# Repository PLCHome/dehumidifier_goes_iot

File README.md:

# My dehumidifier becomes an IoT device

**Please note that opening electrical devices is life-threatening! Opening electrical devices and working on them requires training and authorization.**

**Never work on devices connected to the electrical grid, regardless of whether they are turned on or off.**

**If you follow or replicate parts of this description, you do so entirely at your own risk. I am not liable for any damage caused, including damage to your health and life.**

### Introduction

I've had this TROTEC TTK70 device for many years. It helps me keep my basement dry in the summer.
You can, of course, turn the dehumidifier on every day and let it run for a few hours.
My problem is that I want to use the power from the PV system for this. However, since I leave the house at 6:30 a.m., it doesn't generate enough electricity, depending on the time of year.
At first, I considered using a timer. But this device only beeps once and then stops working when the power comes back on.

## Implementation

**Working with electricity is your own responsibility. I am not liable for any damage, including damage to your health.**

Since the circuit diagram attached to the side was also not informative

I took a look at the device from the inside and noticed that there was a control panel. I drew its circuit diagram and considered how it might work.

The connector has 8 contacts. You can see from the diodes that 1, 2, and 4 are positive, and 3, 5, 6, and 7 are negative.

Since not all LEDs light up at the same time, there must be a control system behind them. I figured that the microcontroller in the device connects lines 3, 5, 6, and 7 to negative one after the other and turns on lines 1, 2, and 4 at the right moment to turn on the LED. We'll refer to lines 3, 5, 6, and 7 as rotating lines.

That leaves the three buttons and line 8. The diodes are there to prevent the wrong LEDs from lighting up when two buttons are pressed at once. And the function is also somewhat instructive. If you pull line eight high with a pull-up resistor, it goes low when the connected rotating line goes negative and the button is pressed.

The only remaining issue is the power supply. However, since the dehumidifier has a transformer built in that always supplies 12V AC when plugged in, that was quickly resolved. Just connect two wires to the output of the rectifier circuit; that's it.

So I gathered a few parts from my stash and started experimenting on the bash board.

I quickly decided to try it with ESPHome and an ESP32-S3 mini that was lying on my desk.

The main problem with the dehumidifier is a microcontroller connected to an LS7805. The ESP32 only requires 3.3V on the GPIOs. If I connect the ESP32 to the same ground via the voltage converter and place the data lines on 3.3V pull-up resistors like the manufacturer did with the buttons, it should work. I didn't even need to solder the pull-ups. They're already built into the ESP32. While lengthening the pins, I noticed that I have two ESP32s that are identical in size but not identical. I have an ESP32-S3 mini and an ESP32-S3 tiny. It's important to note that GPIO 3 is in a different location on both. Since there are boot issues with this GPIO, you shouldn't use GPIO 3. Furthermore, the ESP32-S3 tiny must be installed upside down. Since an ESP32 connected to a 3.3V supply died in another project, I'm now only using 5V voltage converters. However, it seems to be recommended that the ESP generate the 3.3V itself.

Simple transistors should be sufficient for the buttons. Since I don't know the breakdown voltages, I preferred to use diodes there.

Oh, the diodes don't really matter, just like the transistors. I had a large pile of them in stock here. But any other NPN transistor or any other diode will work.

I didn't feel like drawing the ESP, and I couldn't find a finished one. So I just used two connectors.

A friend was kind enough to mill a circuit board for me on his CNC milling machine. It looks a bit better than a perforated board.

After inserting the board into the device, the ESP32 rebooted every time I turned the device on and off. This wasn't good. I then used the other controller from Waveshare. This one also requires upside-down installation and has a different GPIO order. I adjusted the layout so that it now works with both. I modified the underside of the board. The dead copper surface was quite useful here. It works with this one. I also added the capacitor to the board because I was trying to use it to prevent the mini ESP32 from booting. But it seems to be the proximity to the relays and not the supply voltage. The capacitor is 2200uF and is connected to the 5V line to the controller.

## ESPHome and the homeassist

And then the YAML for ESP Home, and here it is in Home Assistant. You can select one of the four modes and OFF using the top selection. The one below allows you to select the integrated timers 2H, 4H, 8H, and OFF. After the controller has selected the setting, it resets to "–" which means nothing is selected there. The states are displayed below as text sensors. There are also two binary sensors for on and water tank full.

When you select a mode, the ESP first checks whether the device is on or off and presses the power button if necessary. The ESP32 then presses the mode button repeatedly until the correct mode is selected.

For the timer, it presses the timer button repeatedly until the selection is made.

Press a button? Not really, it controls the transistors, but to the microcontroller in the dehumidifier, it looks like a button press...

**Working with electricity is your own responsibility. I am not liable for any damage, including damage to your health.**

Do you have such great projects? Write me...

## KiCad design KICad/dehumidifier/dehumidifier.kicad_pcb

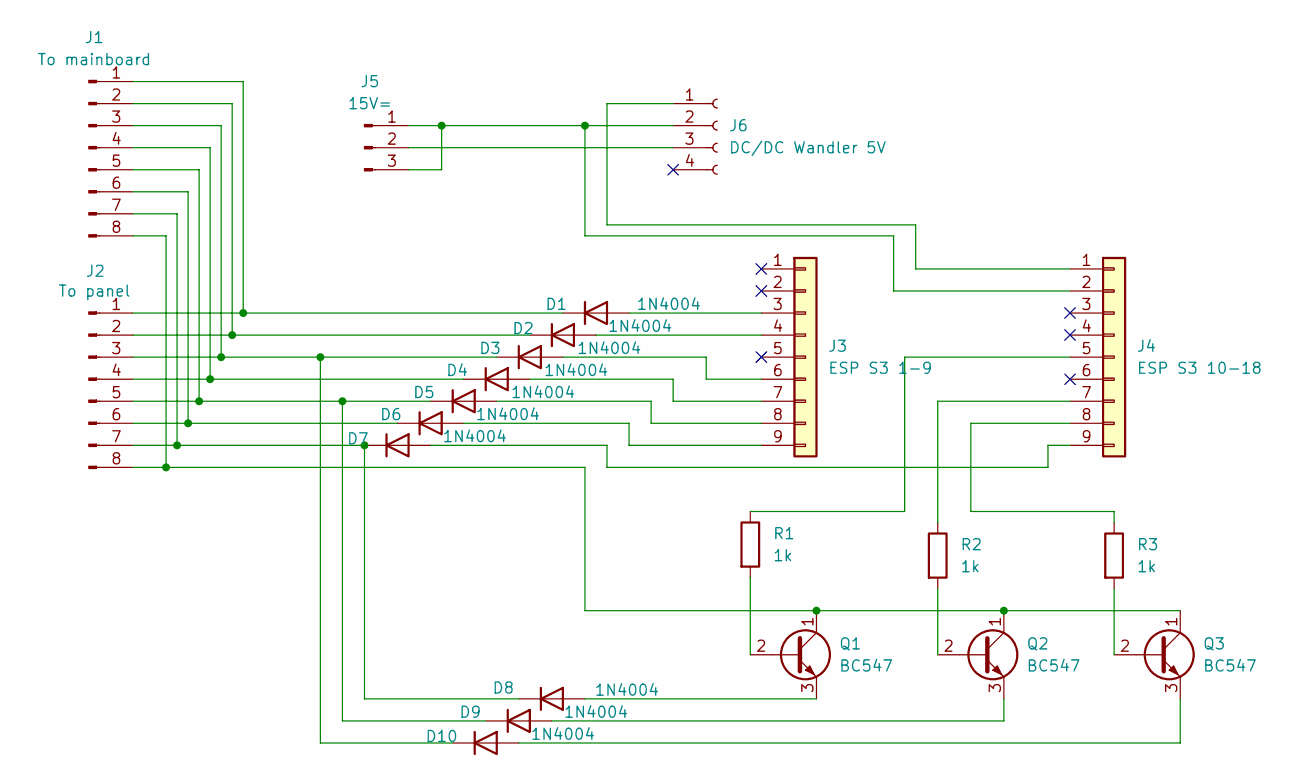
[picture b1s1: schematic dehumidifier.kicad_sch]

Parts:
D1, D2, D3, D4, D5, D6, D7, D8, D9, D10: 1N4004; D_DO-34_SOD68_P7.62mm_Horizontal
J1: To mainboard; PinHeader_1x08_P2.54mm_Vertical
J2: To panel; PinHeader_1x08_P2.54mm_Vertical
J3: ESP S3 1-9; PinHeader_1x09_P2.54mm_Vertical
J4: ESP S3 10-18; PinHeader_1x09_P2.54mm_Vertical
J5: 15V=; PinHeader_1x03_P2.54mm_Vertical
J6: DC/DC Wandler 5V; PinHeader_1x04_P2.54mm_Vertical
Q1, Q2, Q3: BC547; TO-92_Inline
R1, R2, R3: 1k; R_Axial_DIN0207_L6.3mm_D2.5mm_P7.62mm_Horizontal

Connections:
unnamed: D1.2 (A), J3.3
unnamed: D1.1 (K), J1.1, J2.1
unnamed: D2.2 (A), J3.4
unnamed: D2.1 (K), J1.2, J2.2
unnamed: D3.2 (A), J3.6
unnamed: D4.2 (A), J3.7
unnamed: D4.1 (K), J1.4, J2.4
unnamed: D5.2 (A), J3.8
unnamed: D5.1 (K), D9.1 (K), J1.5, J2.5
unnamed: D6.2 (A), J3.9
unnamed: D6.1 (K), J1.6, J2.6
unnamed: D7.2 (A), J4.9
unnamed: D7.1 (K), D8.1 (K), J1.7, J2.7
unnamed: D8.2 (A), Q1.3 (E)
unnamed: D9.2 (A), Q2.3 (E)
unnamed: D10.2 (A), Q3.3 (E)
unnamed: D3.1 (K), D10.1 (K), J1.3, J2.3
unnamed: J1.8, J2.8, Q1.1 (C), Q2.1 (C), Q3.1 (C)
unnamed: J4.1, J6.1
unnamed: J4.2, J5.1, J5.3, J6.2
unnamed: J4.5, R1.1
unnamed: J4.7, R2.1
unnamed: J4.8, R3.1
unnamed: J5.2, J6.3
unnamed: Q1.2 (B), R1.2
unnamed: Q2.2 (B), R2.2
unnamed: Q3.2 (B), R3.2

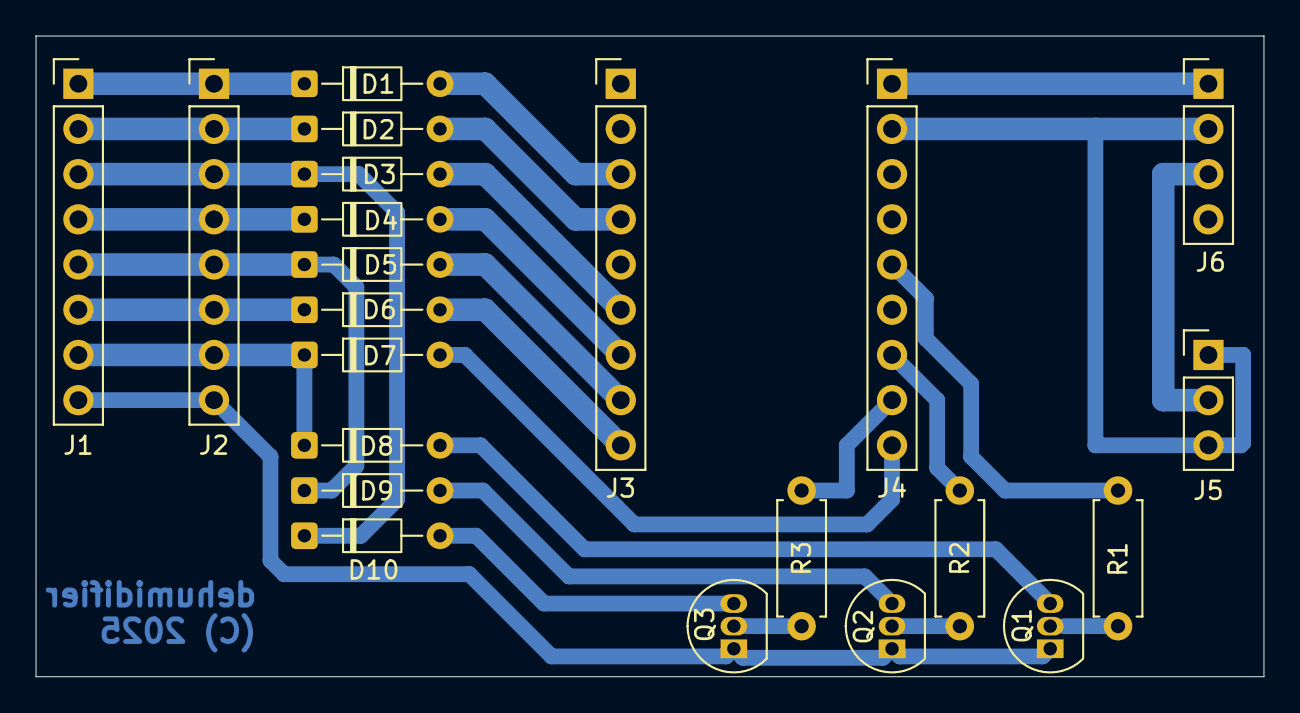
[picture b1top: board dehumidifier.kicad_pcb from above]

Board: 2 copper layers, 69.0 x 36.0 mm, 22 parts (0 on the bottom side), 27 nets.

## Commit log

2025-08-07 first draft
2025-08-07 read.me
2025-08-07 Warnings added
2025-08-07 formatting issue

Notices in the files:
KICad/dehumidifier/dehumidifier.kicad_pcb:
(C) 2025
